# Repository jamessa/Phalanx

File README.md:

# Phalanx

Phalanx /ˈfælæŋks/ 「手趾骨」是我為了要找到一個可以快速實驗各種鍵盤配置的方法而設計的四按鍵的PCB。

這設計參考了[Saoto Tsuchiya](https://github.com/saoto28/pineapple60/blob/main/p4/README.md)的測試模組，加以簡化而成。

搭配熱插拔後，就可以快速的實驗各種鍵盤配置。

在幾天的時間內，我就找到我理想的鍵盤配置了,我稱它為「[務實](https://github.com/jamessa/Pragmatic)34」。

PCB

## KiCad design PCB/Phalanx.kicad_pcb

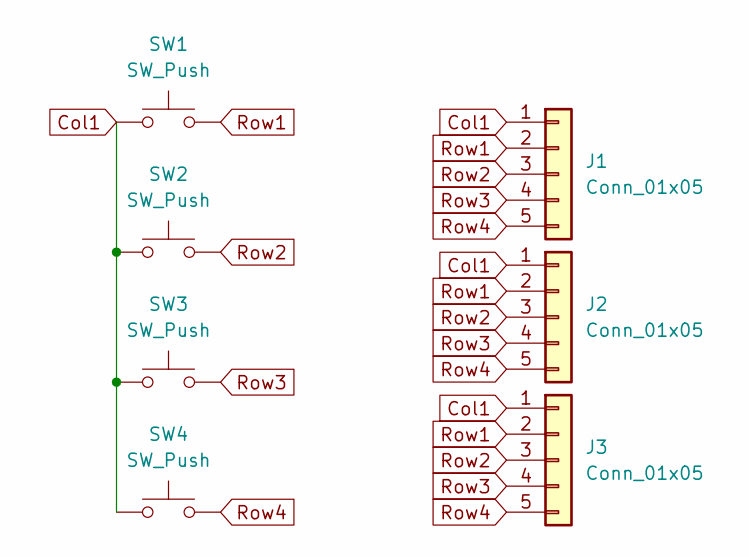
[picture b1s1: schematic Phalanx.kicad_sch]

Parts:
J1, J2, J3: Conn_01x05; PinHeader_1x05_P2.54mm_Vertical
SW1, SW2, SW3, SW4: SW_Push; CherryMX_Hotswap

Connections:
Col1: J1.1, J2.1, J3.1, SW1.1, SW2.1, SW3.1, SW4.1
Row1: J1.2, J2.2, J3.2, SW1.2
Row2: J1.3, J2.3, J3.3, SW2.2
Row3: J1.4, J2.4, J3.4, SW3.2
Row4: J1.5, J2.5, J3.5, SW4.2

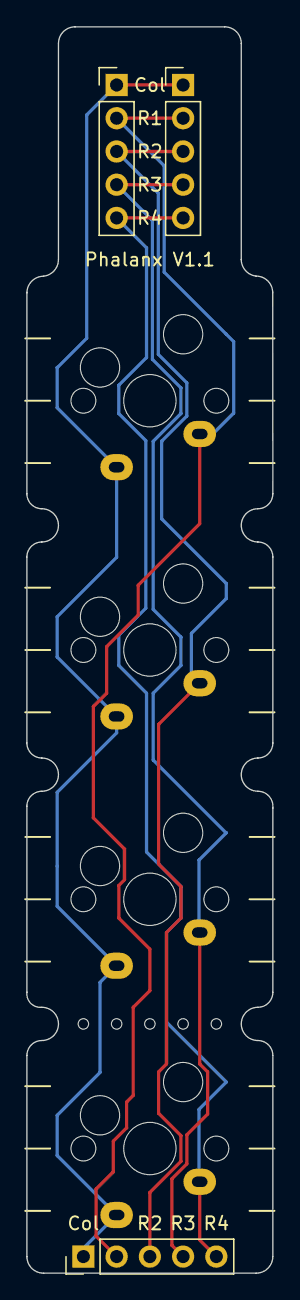
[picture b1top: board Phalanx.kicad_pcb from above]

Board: 2 copper layers, 18.8 x 95.2 mm, 7 parts (0 on the bottom side), 5 nets.

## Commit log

2022-01-31 init
2022-03-18 fix dimensions
2022-03-19 readme
2022-03-19 reduce image size
2022-03-29 update fabrication file
